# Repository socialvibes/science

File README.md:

science
=======

Social Vibes research stuff

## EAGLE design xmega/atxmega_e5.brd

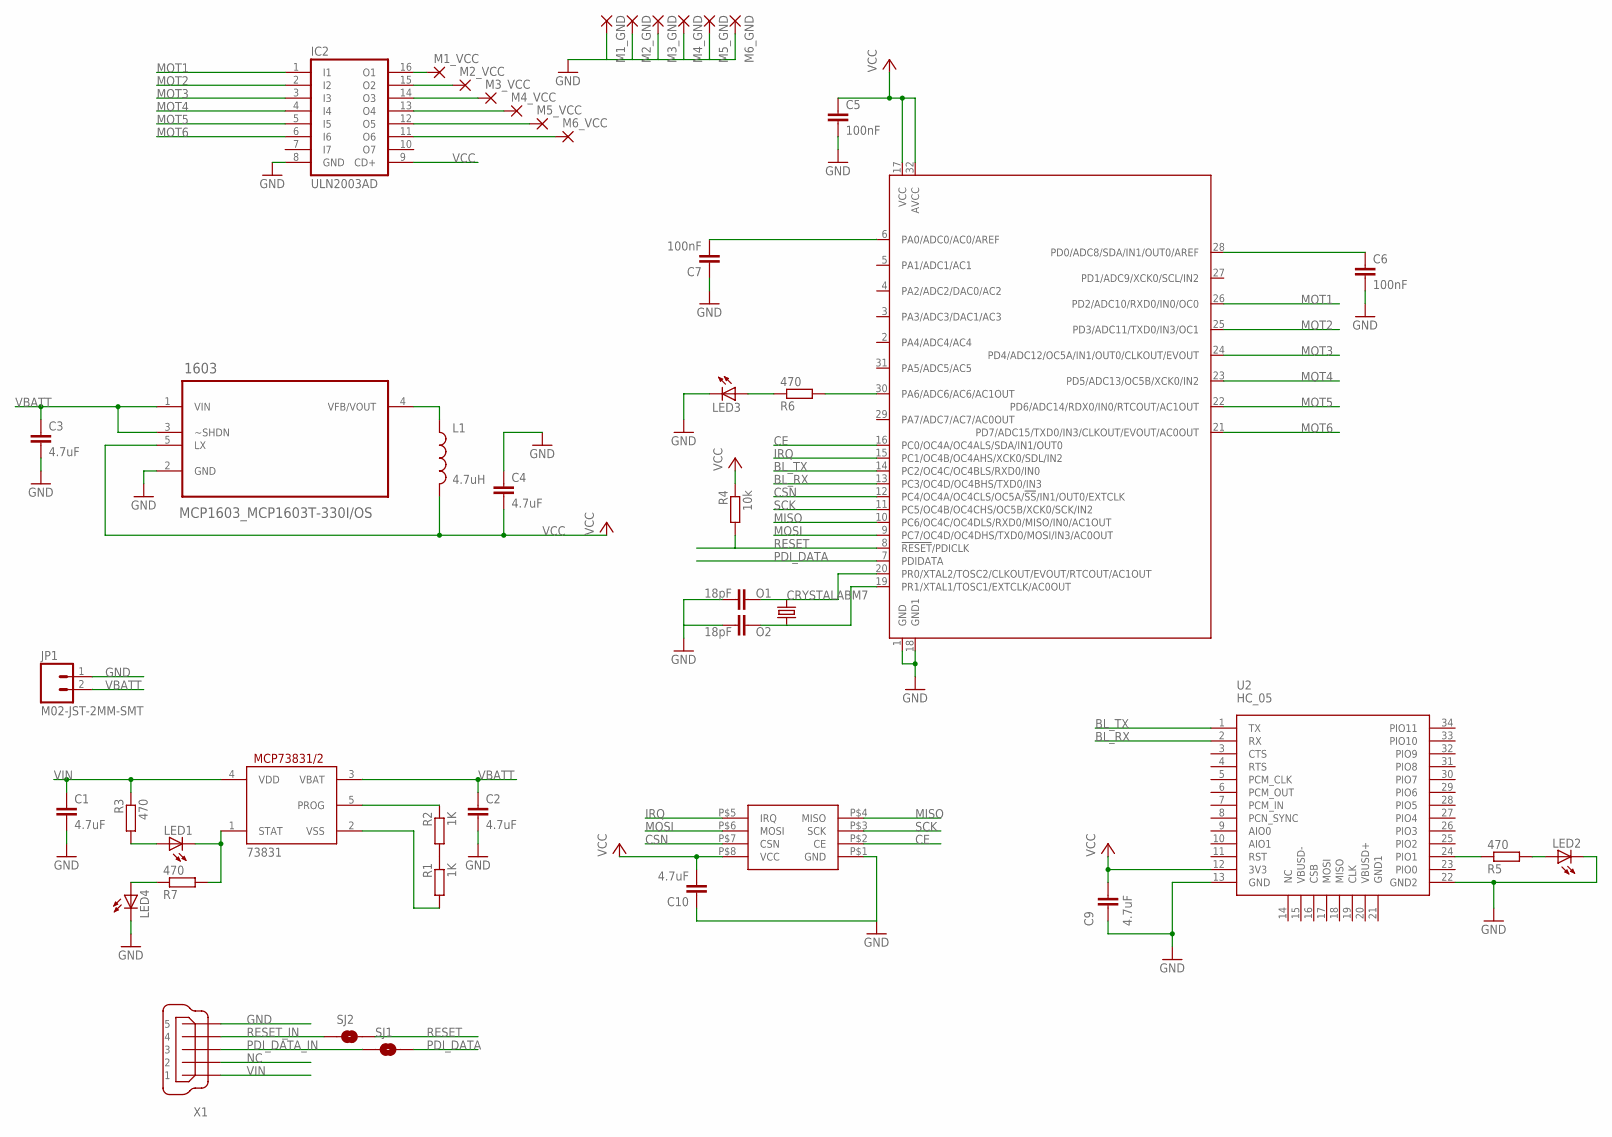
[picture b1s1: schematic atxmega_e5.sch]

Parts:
1603: MCP1603_MCP1603T-330I/OS; MCP1603_SOT95P280X110-5N
73831: MCP73831/OT; SOT23-5L
C1, C2, C3, C4, C9, C10: 4.7uF; C0603K
C5, C6, C7: 100nF; C0603K
IC2: ULN2003AD; SO16
JP1: M02-JST-2MM-SMT; JST-2-SMD
L1: 4.7uH; 1007
LED1, LED2, LED3, LED4: LED0805LED; 0805LED
M1_GND, M1_VCC, M2_GND, M2_VCC, M3_GND, M3_VCC, M4_GND, M4_VCC, M5_GND, M5_VCC, M6_GND, M6_VCC: WIREPAD2,15/1,0; 2,15/1,0
O1, O2: 18pF; C0603K
R1, R2: 1K; R0603
R3, R5, R6, R7: 470; R0603
R4: 10k; R0603
SJ1, SJ2: SOLDERJUMPERNO; SJ_2S-NO
U1: ATXMEGAE5AU; TQFP32
U2: HC_05; BLUETOOTH_SMD
U$1: CRYSTALABM7; ABM7
U$2: NRF24L01+
X1: MINI-USB-32005-201; 32005-201

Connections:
BL_RX: U1.13 (PC3/OC4D/OC4BHS/TXD0/IN3), U2.2 (RX)
BL_TX: U1.14 (PC2/OC4C/OC4BLS/RXD0/IN0), U2.1 (TX)
CE: U1.16 (PC0/OC4A/OC4ALS/SDA/IN1/OUT0), U$2.P$2 (CE)
CSN: U1.12 (PC4/OC4A/OC4CLS/OC5A/!SS!/IN1/OUT0/EXTC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), U$2.P$7 (CSN)
GND: 1603.2 (GND), C1.2, C2.2, C3.2, C4.1, C5.2, C6.2, C7.1, C9.2, C10.1, IC2.8 (GND), JP1.1 (2), LED2.C, LED3.C, LED4.C, M1_GND.1, M2_GND.1, M3_GND.1, M4_GND.1, M5_GND.1, M6_GND.1, O1.2, O2.2, U1.1 (GND), U1.18 (GND1), U2.13 (GND), U2.22 (GND2), U$2.P$1 (GND), X1.5
IRQ: U1.15 (PC1/OC4B/OC4AHS/XCK0/SDL/IN2), U$2.P$5 (IRQ)
MISO: U1.10 (PC6/OC4C/OC4DLS/RXD0/MISO/IN0/AC1OUT), U$2.P$4 (MISO)
MOSI: U1.9 (PC7/OC4D/OC4DHS/TXD0/MOSI/IN3/AC0OUT), U$2.P$6 (MOSI)
MOT1: IC2.1 (I1), U1.26 (PD2/ADC10/RXD0/IN0/OC0)
MOT2: IC2.2 (I2), U1.25 (PD3/ADC11/TXD0/IN3/OC1)
MOT3: IC2.3 (I3), U1.24 (PD4/ADC12/OC5A/IN1/OUT0/CLKOUT/EVOUT)
MOT4: IC2.4 (I4), U1.23 (PD5/ADC13/OC5B/XCK0/IN2)
MOT5: IC2.5 (I5), U1.22 (PD6/ADC14/RDX0/IN0/RTCOUT/AC1OUT)
MOT6: IC2.6 (I6), U1.21 (PD7/ADC15/TXD0/IN3/CLKOUT/EVOUT/AC0OUT)
unnamed: O1.1, U1.20 (PR0/XTAL2/TOSC2/CLKOUT/EVOUT/RTCOUT/AC1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), U$1.P$2 (2)
unnamed: IC2.16 (O1), M1_VCC.1
unnamed: IC2.15 (O2), M2_VCC.1
unnamed: IC2.14 (O3), M3_VCC.1
unnamed: IC2.13 (O4), M4_VCC.1
unnamed: IC2.12 (O5), M5_VCC.1
unnamed: IC2.11 (O6), M6_VCC.1
unnamed: O2.1, U1.19 (PR1/XTAL1/TOSC1/EXTCLK/AC0OUT), U$1.P$1 (1)
unnamed: 1603.4 (VFB/VOUT), L1.1
unnamed: LED1.A, R3.2
unnamed: 73831.1 (STAT), LED1.C, R7.2
unnamed: 73831.5 (PROG), R2.1
unnamed: R1.1, R2.2
unnamed: 73831.2 (VSS), R1.2
unnamed: LED3.A, R6.1
unnamed: R6.2, U1.30 (PA6/ADC6/AC6/AC1OUT)
unnamed: LED4.A, R7.1
unnamed: LED2.A, R5.2
unnamed: R5.1, U2.24 (PIO1)
unnamed: C6.1, U1.28 (PD0/ADC8/SDA/IN1/OUT0/AREF)
unnamed: C7.2, U1.6 (PA0/ADC0/AC0/AREF)
NC: X1.2
PDI_DATA: SJ1.2, U1.7 (PDIDATA)
PDI_DATA_IN: SJ1.1, X1.3
RESET: R4.2, SJ2.2, U1.8 (!RESET!/PDICLK)
RESET_IN: SJ2.1, X1.4
SCK: U1.11 (PC5/OC4B/OC4CHS/OC5B/XCK0/SCK/IN2), U$2.P$3 (SCK)
VBATT: 1603.1 (VIN), 1603.3 (~SHDN), 73831.3 (VBAT), C2.1, C3.1, JP1.2 (1)
VCC: 1603.5 (LX), C4.2, C5.1, C9.1, C10.2, IC2.9 (CD+), L1.2, R4.1, U1.17 (VCC), U1.32 (AVCC), U2.12 (3V3), U$2.P$8 (VCC)
VIN: 73831.4 (VDD), C1.1, R3.1, X1.1

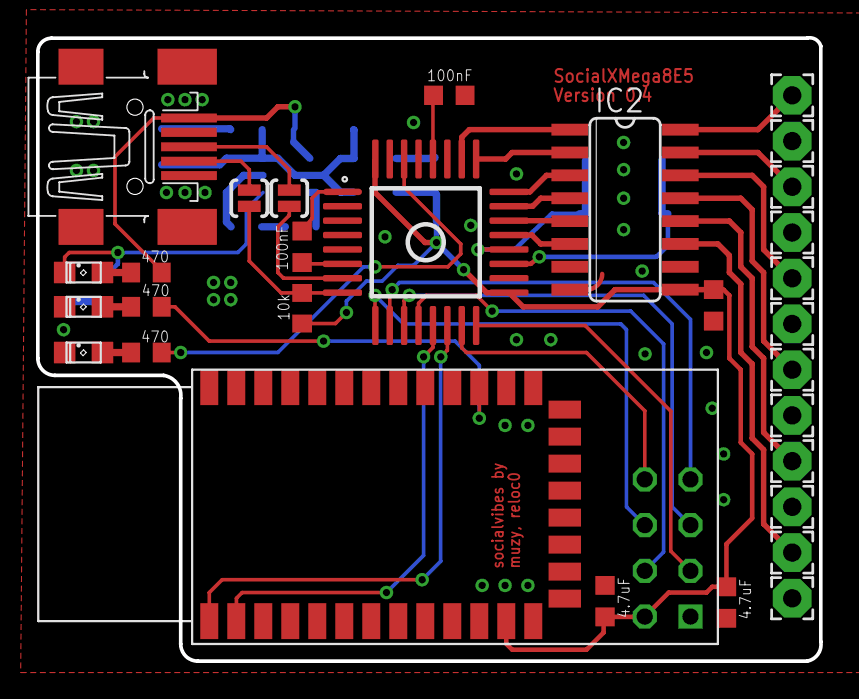
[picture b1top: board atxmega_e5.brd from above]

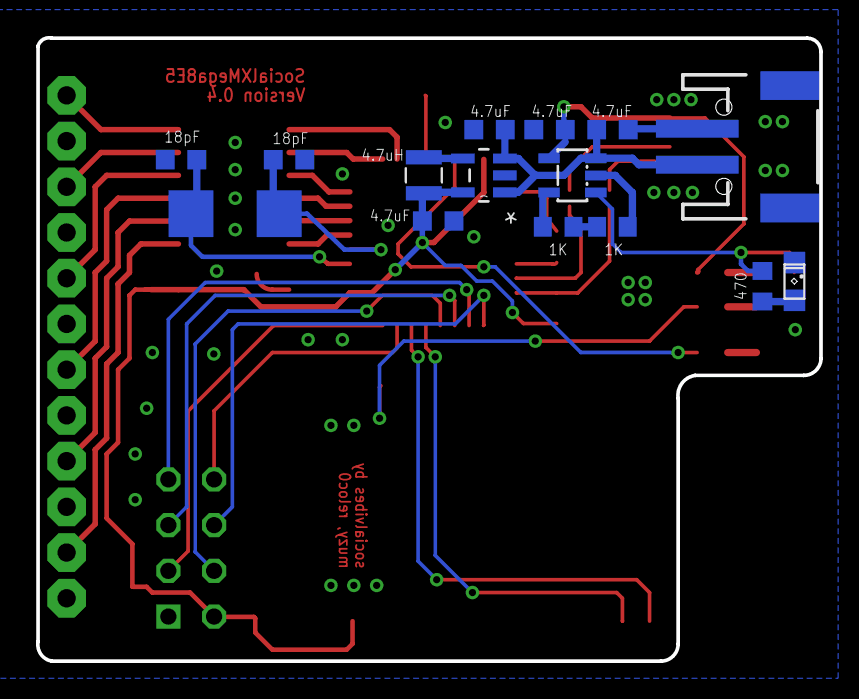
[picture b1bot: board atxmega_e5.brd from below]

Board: 2 copper layers, 43.5 x 34.6 mm, 46 parts (15 on the bottom side), 43 nets.

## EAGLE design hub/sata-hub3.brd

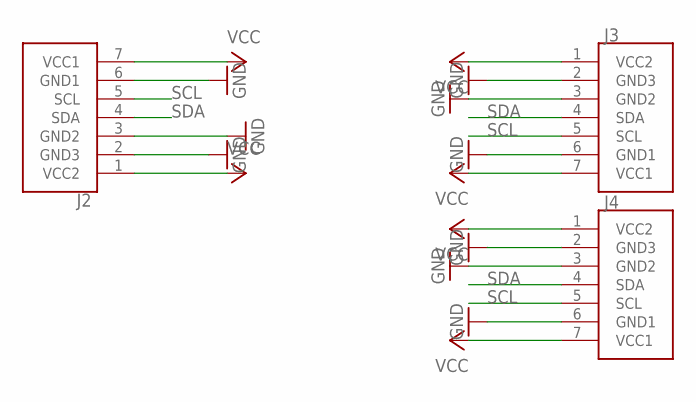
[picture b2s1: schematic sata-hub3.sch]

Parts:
J2, J3, J4: SATA7-RA

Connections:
GND: J2.2 (GND3), J2.3 (GND2), J2.6 (GND1), J3.2 (GND3), J3.3 (GND2), J3.6 (GND1), J4.2 (GND3), J4.3 (GND2), J4.6 (GND1)
SCL: J2.5 (SCL), J3.5 (SCL), J4.5 (SCL)
SDA: J2.4 (SDA), J3.4 (SDA), J4.4 (SDA)
VCC: J2.1 (VCC2), J2.7 (VCC1), J3.1 (VCC2), J3.7 (VCC1), J4.1 (VCC2), J4.7 (VCC1)

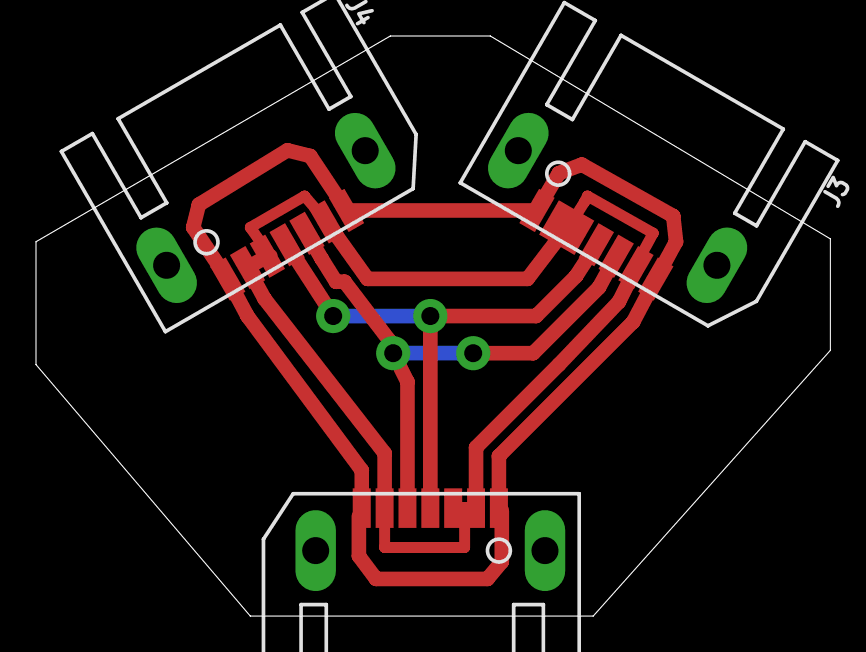
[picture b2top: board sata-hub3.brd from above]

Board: 2 copper layers, 44.1 x 32.2 mm, 3 parts (0 on the bottom side), 4 nets.

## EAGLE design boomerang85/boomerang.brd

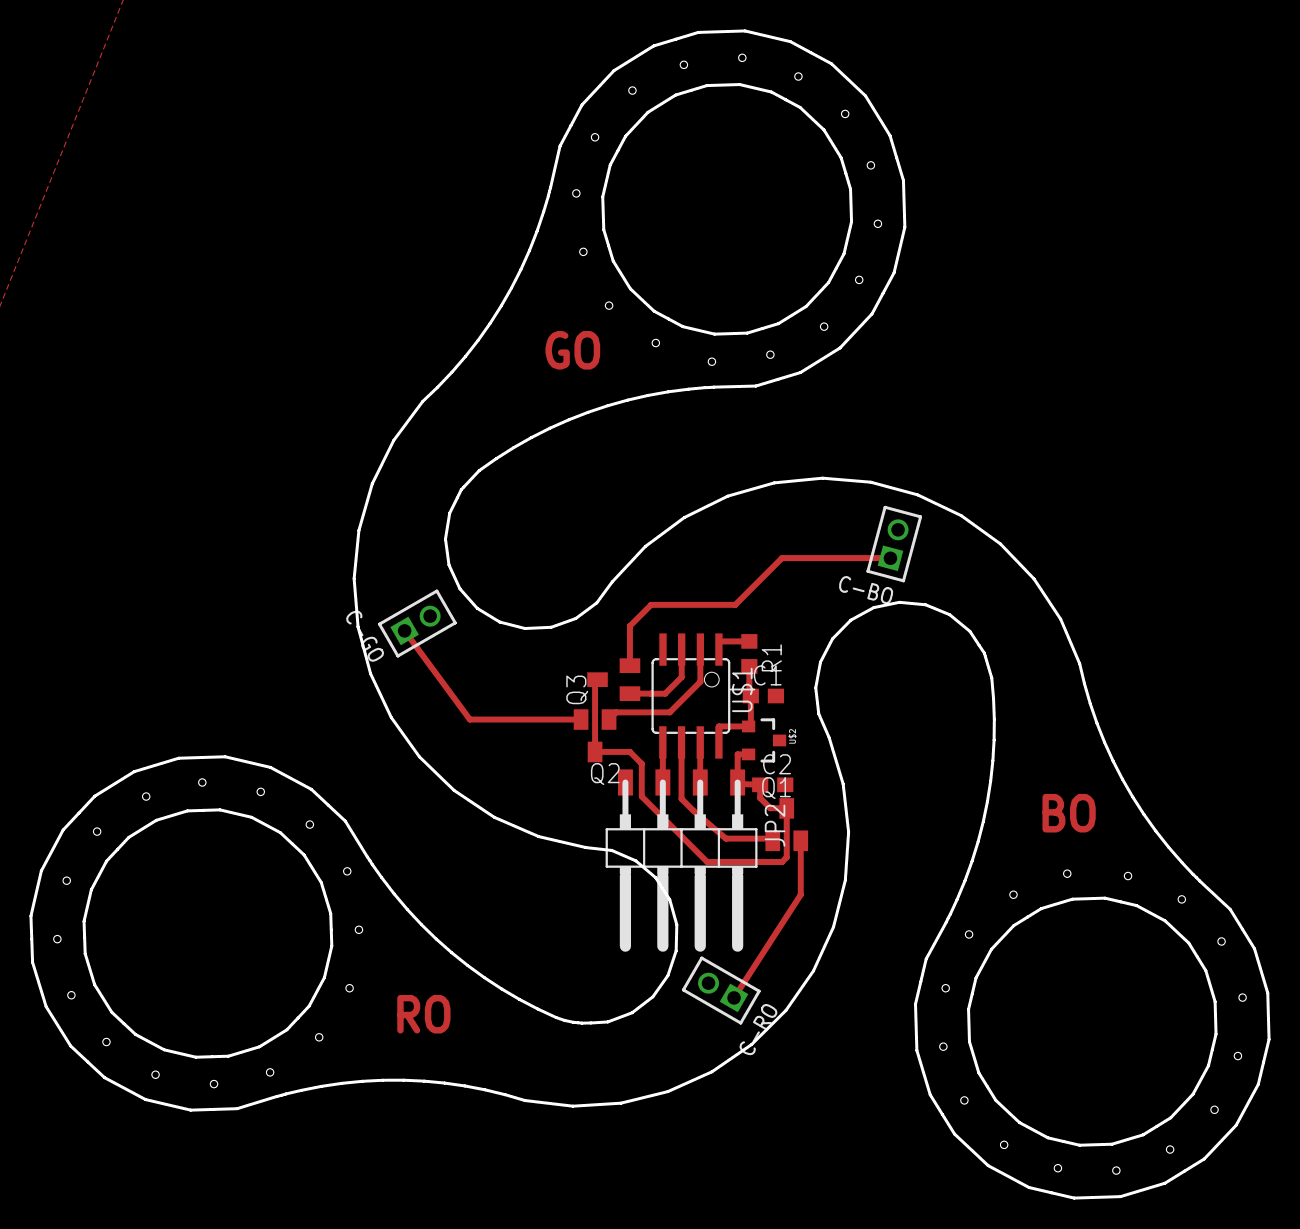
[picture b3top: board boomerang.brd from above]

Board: 2 copper layers, 84.1 x 79.3 mm, 12 parts (0 on the bottom side), 12 nets.

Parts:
C1, C2: 100nF; C0603
C-BO: 1X02M
C-GO: 1X02M
C-RO: 1X02M
JP2: 1X04SMD/90
Q1, Q2, Q3: SOT23
R1: 10K; R0603
U$1: TINY25/45/85-20SU; SOIC8
U$2: LM3480IM4; SOT23-3

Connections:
B: Q3.1, U$1.3
BO: C-BO.1, Q3.2
G: Q2.1, U$1.2
GND: C1.2, C2.2, C-BO.2, C-GO.2, C-RO.2, JP2.4, U$1.4, U$2.3
GO: C-GO.1, Q2.2
R: Q1.1, U$1.6
RES: R1.1, U$1.1
RO: C-RO.1, Q1.2
SCL: JP2.2, U$1.7
SDA: JP2.3, U$1.5
VCC: C2.1, JP2.1, Q1.3, Q2.3, Q3.3, U$2.2
VCC_GOOD: C1.1, R1.2, U$1.8, U$2.1

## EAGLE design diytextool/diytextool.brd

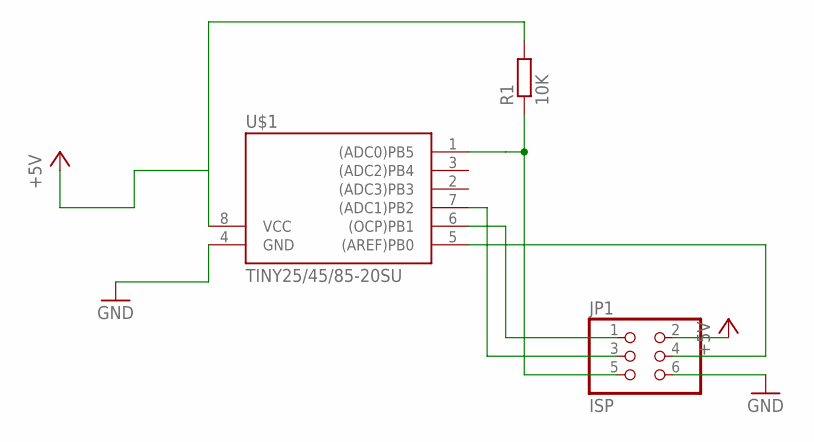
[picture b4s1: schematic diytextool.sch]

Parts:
JP1: ISP; 2X03SMD
R1: 10K; R0603
U$1: TINY25/45/85-20SU; SOIC8

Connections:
+5V: JP1.2, R1.2, U$1.8 (VCC)
GND: JP1.6, U$1.4 (GND)
unnamed: JP1.5, R1.1, U$1.1 ((ADC0)PB5)
unnamed: JP1.4, U$1.5 ((AREF)PB0)
unnamed: JP1.3, U$1.7 ((ADC1)PB2)
unnamed: JP1.1, U$1.6 ((OCP)PB1)

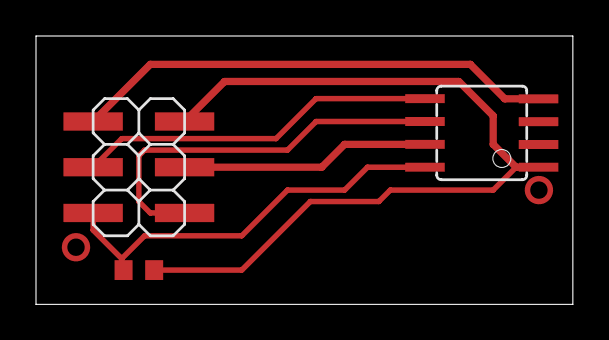
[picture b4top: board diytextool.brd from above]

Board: 2 copper layers, 29.8 x 14.9 mm, 3 parts (0 on the bottom side), 6 nets.

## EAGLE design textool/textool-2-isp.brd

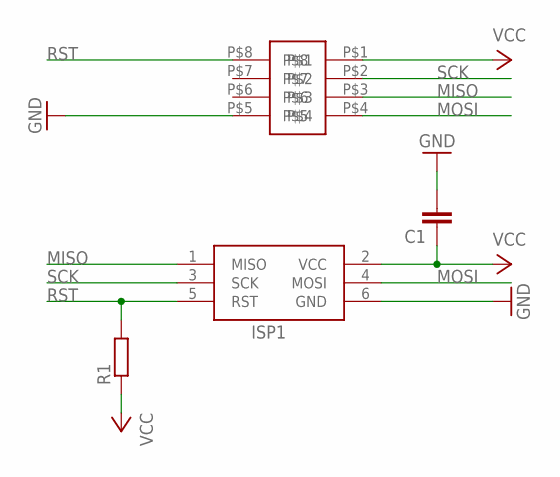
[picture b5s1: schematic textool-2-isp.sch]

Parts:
C1: C-EUC0603; C0603
ISP1: AVRISP-6; AVRISP
R1: R-EU_R0603; R0603
U$1: TEXTOOL

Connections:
GND: C1.2, ISP1.6 (GND), U$1.P$5
MISO: ISP1.1 (MISO), U$1.P$3
MOSI: ISP1.4 (MOSI), U$1.P$4
RST: ISP1.5 (RST), R1.2, U$1.P$8
SCK: ISP1.3 (SCK), U$1.P$2
VCC: C1.1, ISP1.2 (VCC), R1.1, U$1.P$1

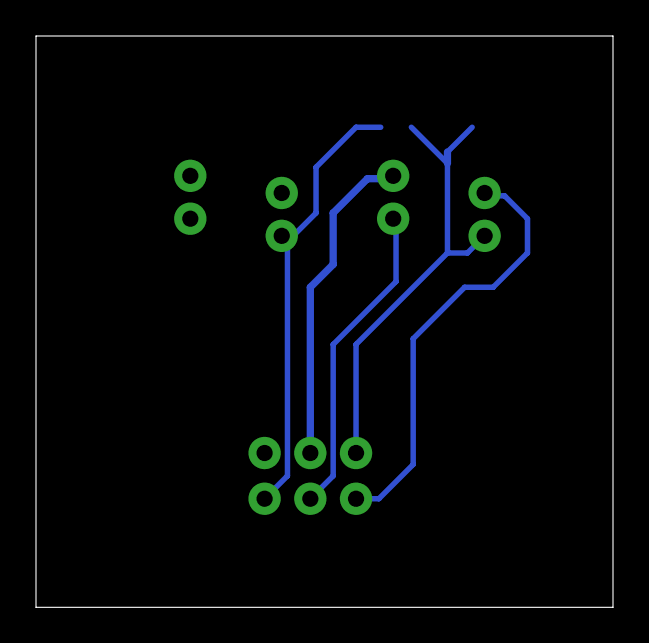
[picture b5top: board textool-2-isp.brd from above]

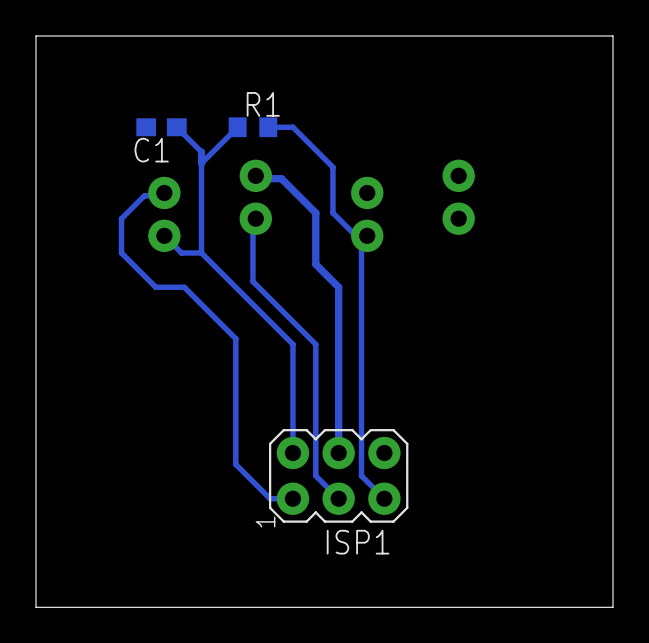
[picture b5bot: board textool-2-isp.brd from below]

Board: 2 copper layers, 32.1 x 31.7 mm, 4 parts (4 on the bottom side), 6 nets.

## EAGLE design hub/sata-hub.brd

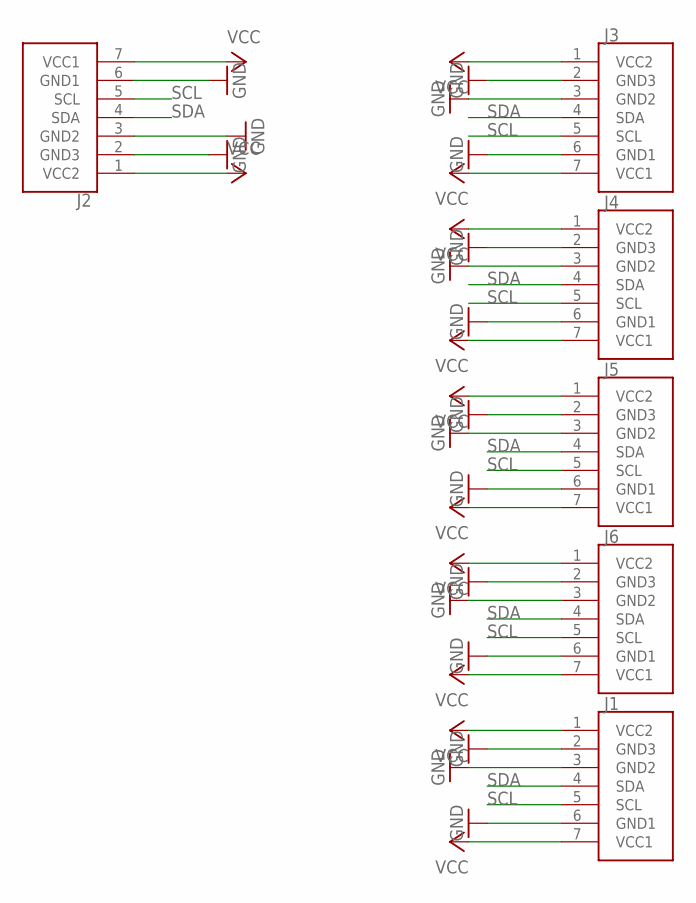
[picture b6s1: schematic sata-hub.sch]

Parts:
J1, J2, J3, J4, J5, J6: SATA7-RA

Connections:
GND: J1.2 (GND3), J1.3 (GND2), J1.6 (GND1), J2.2 (GND3), J2.3 (GND2), J2.6 (GND1), J3.2 (GND3), J3.3 (GND2), J3.6 (GND1), J4.2 (GND3), J4.3 (GND2), J4.6 (GND1), J5.2 (GND3), J5.3 (GND2), J5.6 (GND1), J6.2 (GND3), J6.3 (GND2), J6.6 (GND1)
SCL: J1.5 (SCL), J2.5 (SCL), J3.5 (SCL), J4.5 (SCL), J5.5 (SCL), J6.5 (SCL)
SDA: J1.4 (SDA), J2.4 (SDA), J3.4 (SDA), J4.4 (SDA), J5.4 (SDA), J6.4 (SDA)
VCC: J1.1 (VCC2), J1.7 (VCC1), J2.1 (VCC2), J2.7 (VCC1), J3.1 (VCC2), J3.7 (VCC1), J4.1 (VCC2), J4.7 (VCC1), J5.1 (VCC2), J5.7 (VCC1), J6.1 (VCC2), J6.7 (VCC1)

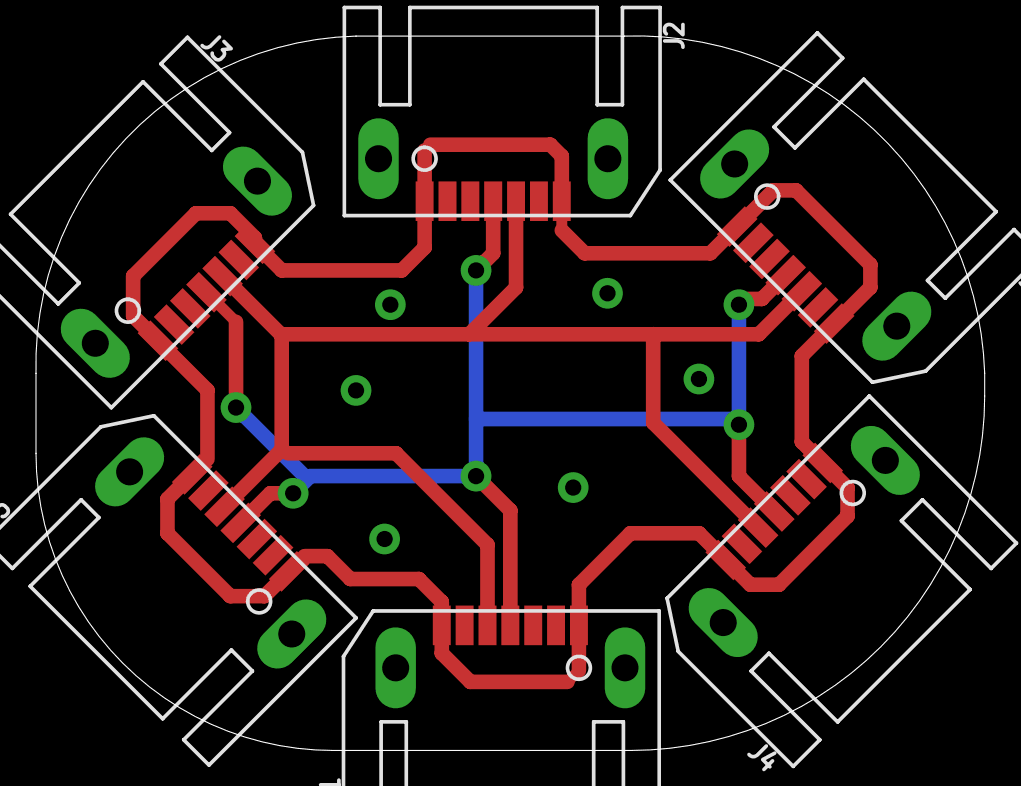
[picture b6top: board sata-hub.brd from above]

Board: 2 copper layers, 52.7 x 39.7 mm, 6 parts (0 on the bottom side), 4 nets.

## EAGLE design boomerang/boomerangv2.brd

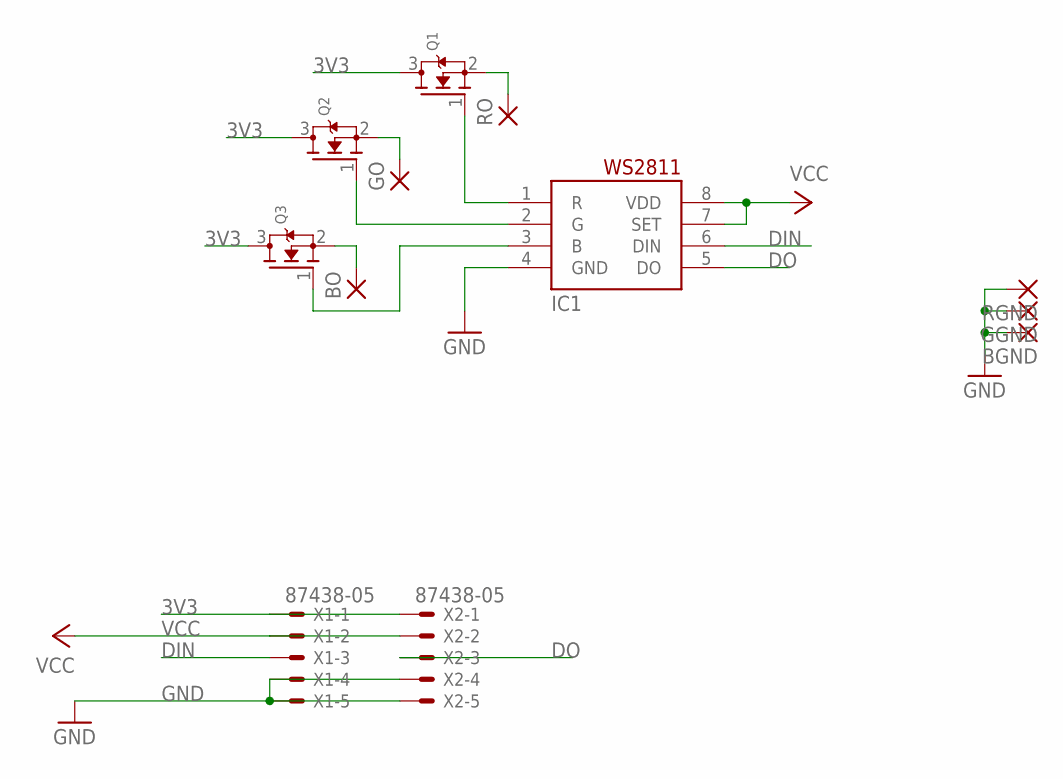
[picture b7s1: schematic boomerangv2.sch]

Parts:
BGND: SMD2; SMD1,27-2,54
BO: SMD2; SMD1,27-2,54
GGND: SMD2; SMD1,27-2,54
GO: SMD2; SMD1,27-2,54
IC1: WS2811-SOP8; SO08-SKINNYPADS
Q1, Q2, Q3: MOSFET-NREFLOW; SOT23
RGND: SMD2; SMD1,27-2,54
RO: SMD2; SMD1,27-2,54
X1, X2: 87438-05

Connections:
3V3: Q1.3 (D), Q2.3 (D), Q3.3 (D), X1.1, X2.1
B: IC1.3 (B), Q3.1 (G)
BO: BO.1, Q3.2 (S)
DIN: IC1.6 (DIN), X1.3
DO: IC1.5 (DO), X2.3
G: IC1.2 (G), Q2.1 (G)
GND: BGND.1, GGND.1, IC1.4 (GND), RGND.1, X1.4, X1.5, X2.4, X2.5
GO: GO.1, Q2.2 (S)
R: IC1.1 (R), Q1.1 (G)
RO: Q1.2 (S), RO.1
VCC: IC1.7 (SET), IC1.8 (VDD), X1.2, X2.2

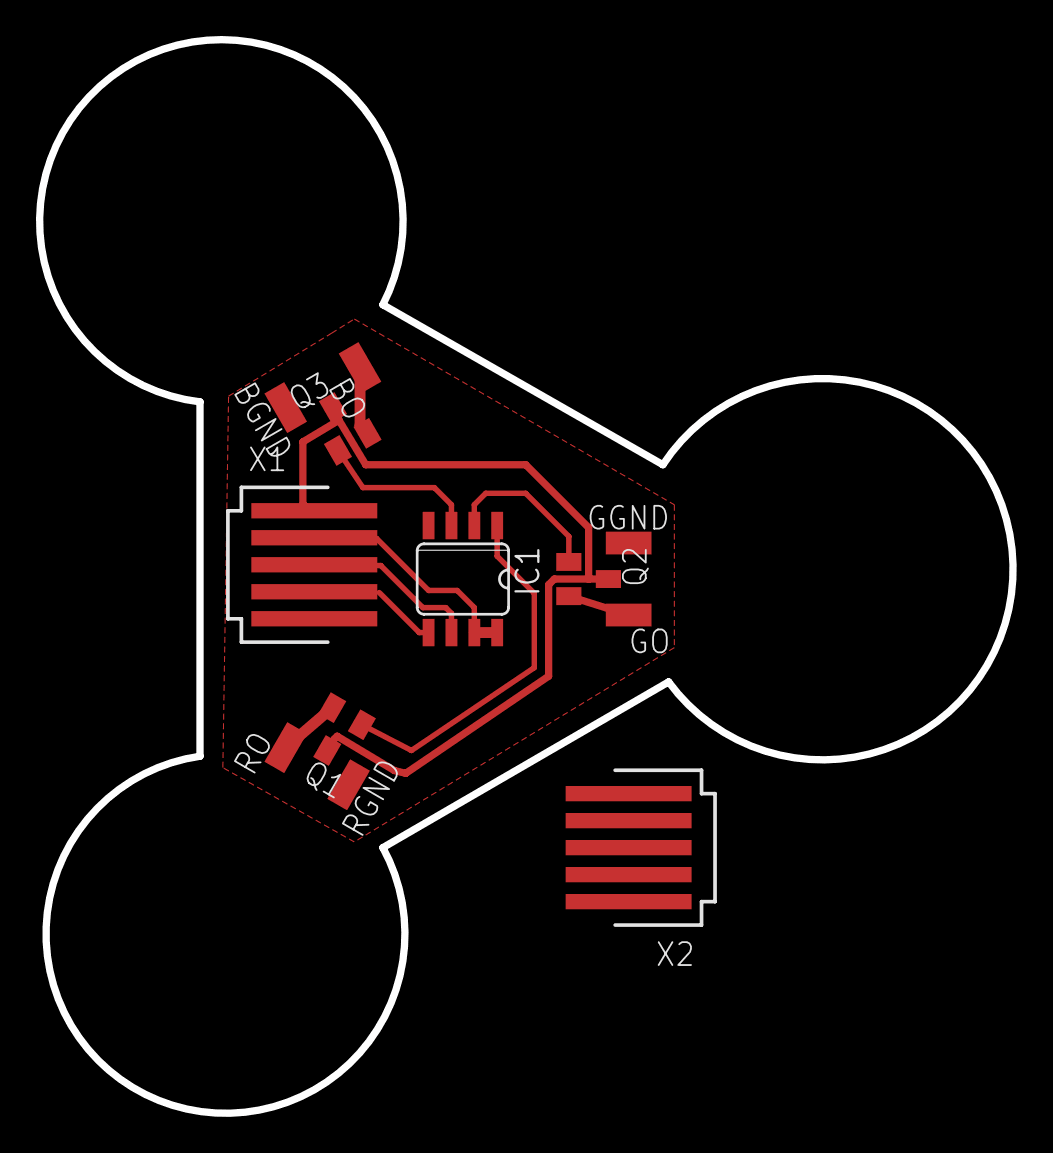
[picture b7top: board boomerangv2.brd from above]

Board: 2 copper layers, 54.1 x 59.6 mm, 12 parts (0 on the bottom side), 11 nets.

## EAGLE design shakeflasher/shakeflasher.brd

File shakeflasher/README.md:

shakeflasher
============

this is a subproject that was put on a thin pcb. We tried to wash the pcbs afterwards.

result: washing pcbs does not seem to be a problem.

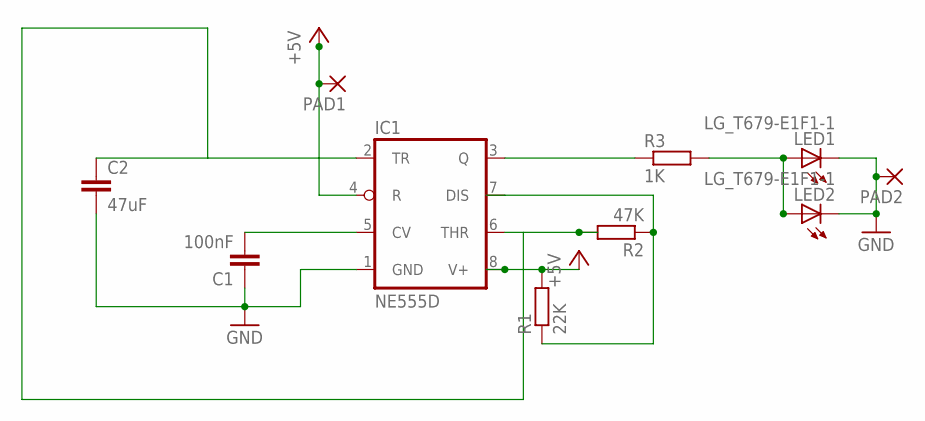
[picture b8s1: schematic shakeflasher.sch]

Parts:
C1: 100nF; C0805
C2: 47uF; C0805
IC1: NE555D; SO08
LED1, LED2: LG_T679-E1F1-1; PLCC2
PAD1, PAD2: SMD5; SMD2,54-5,08
R1: 22K; R0805
R2: 47K; R0805
R3: 1K; R0805

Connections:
+5V: IC1.4 (R), IC1.8 (V+), PAD1.1, R1.2
GND: C1.1, C2.2, IC1.1 (GND), LED1.C, LED2.C, PAD2.1
unnamed: LED1.A, LED2.A, R3.2
unnamed: IC1.3 (Q), R3.1
unnamed: IC1.7 (DIS), R1.1, R2.1
unnamed: C2.1, IC1.2 (TR), IC1.6 (THR), R2.2
V: C1.2, IC1.5 (CV)

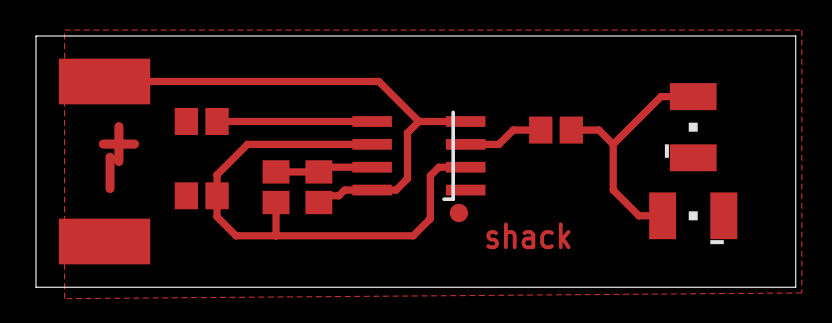
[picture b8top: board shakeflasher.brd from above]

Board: 2 copper layers, 42.2 x 14.0 mm, 10 parts (0 on the bottom side), 7 nets.

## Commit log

2013-06-21 Not so initital commit
2013-06-23 moar
2013-07-11 restructured repository, added small piece of documentation for the shakeflasher
2013-07-11 documentation on the pulse width modulation experiments
2013-07-12 definition of the study to vibration motors
2013-11-14 boomerang testschaltung (ugly)
2013-11-14 nicer :)
2013-11-15 one layer in time
2013-11-15 OCD for everyone
2014-01-04 moar awesome
2014-01-24 updated SATA - connector part in library used
2014-01-24 added sata cable hub
2014-01-24 forgot to make a trace taller
2014-01-24 nicer
2014-01-25 made the holes on the 3-hub easier to drill
2014-03-01 fixed version of textool adapter
2014-03-01 fixes, design improvements
2014-06-05 new revision (ready for OSHpark)

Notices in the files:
parts and their libraries:
SparkFun-PowerIC: Licensing: CC v3.0 Share-Alike You are welcome to use this library for commercial purposes.
SparkFun-Passives: Licensing: Creative Commons ShareAlike 4.0 International - https://creativecommons.org/licenses/by-sa/4.0
